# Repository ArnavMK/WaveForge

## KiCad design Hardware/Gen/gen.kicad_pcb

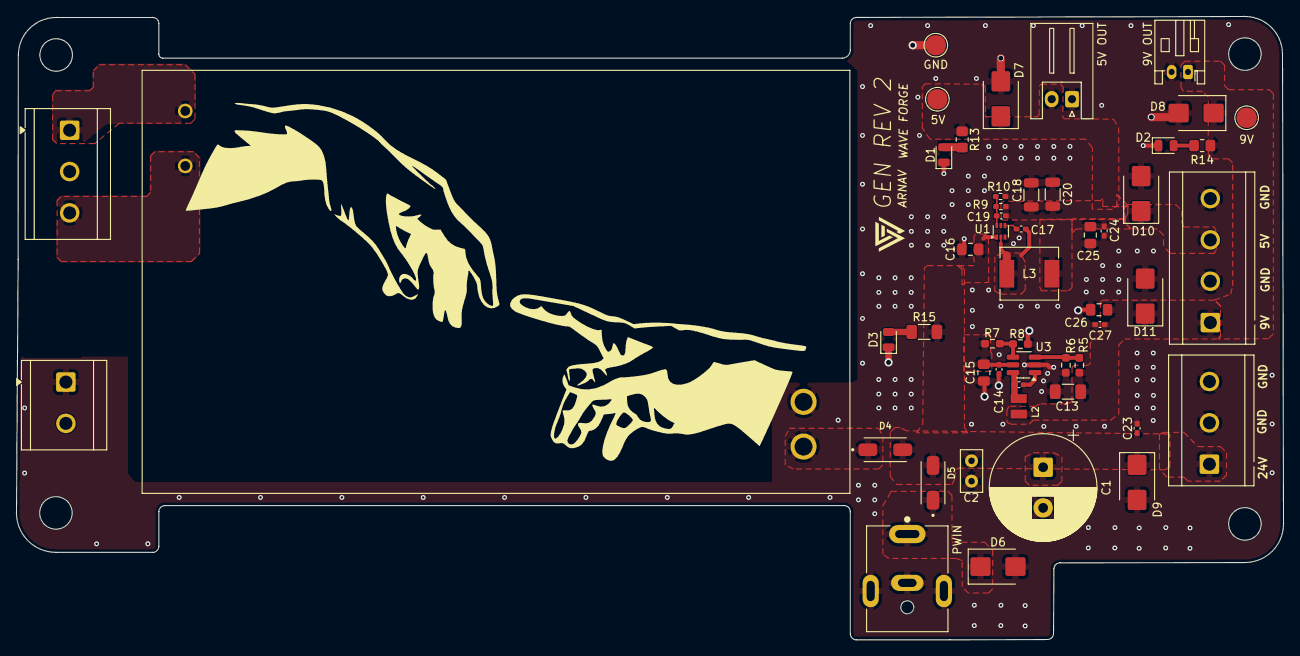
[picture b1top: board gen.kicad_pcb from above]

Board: 2 copper layers, 155.8 x 76.6 mm, 55 parts (0 on the bottom side), 18 nets.

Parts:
5V, 9V: TestPoint; TestPoint_Pad_D2.5mm
5V OUT: SHORI; JST_XH_S2B-XH-A_1x02_P2.50mm_Horizontal
9V OUT: MAE; JST_PH_S2B-PH-K_1x02_P2.00mm_Horizontal
C1: 1000uF; CP_Radial_D13.0mm_P5.00mm
C2: 1uF; C_Disc_D5.0mm_W2.5mm_P2.50mm
C12, C14, C17, C23, C24, C27: 100nF; C_0402_1005Metric_Pad0.74x0.62mm_HandSolder
C13: 15uF; C_1206_3216Metric_Pad1.33x1.80mm_HandSolder
C15: 4.7uF; C_0805_2012Metric_Pad1.18x1.45mm_HandSolder
C16: 3.3uF; C_0805_2012Metric_Pad1.18x1.45mm_HandSolder
C18, C20: 47uF; C_1206_3216Metric
C19: 82pF; C_0402_1005Metric_Pad0.74x0.62mm_HandSolder
C25, C26: 10uF; C_0805_2012Metric_Pad1.18x1.45mm_HandSolder
D1, D2, D3: LED; LED_0805_2012Metric
D4, D5: B340; DIOM5226X240N
D6, D9: SMBJ28A; D_SMB
D7, D8, D10, D11: SMBJ6.0A; D_SMB
GND: TestPoint; TestPoint_Pad_D2.5mm
H1, H2, H3, H3#2: MountingHole; MountingHole_4mm
J1: Screw_Terminal_01x03; TerminalBlock_CUI_TB007-508-03_1x03_P5.08mm_Horizontal
J2: XLR4; TerminalBlock_CUI_TB007-508-04_1x04_P5.08mm_Horizontal
J3: XLR3; TerminalBlock_CUI_TB007-508-03_1x03_P5.08mm_Horizontal
L2: 68uH; WE-LQS_2512
L3: 10uH; IND_SRP6540-100M
MAINS TO GROUND: Screw_Terminal_01x02; TerminalBlock_CUI_TB007-508-02_1x02_P5.08mm_Horizontal
PS1: IRM-90-24; CONV_IRM-90-24
PWIN: PJ-063BH; CUI_PJ-063BH
R5: 178K; R_0603_1608Metric_Pad0.98x0.95mm_HandSolder
R6: 22.1K; R_0603_1608Metric_Pad0.98x0.95mm_HandSolder
R7: 1.37M; R_0603_1608Metric_Pad0.98x0.95mm_HandSolder
R8: 255K; R_0603_1608Metric_Pad0.98x0.95mm_HandSolder
R9: 107K; R_0402_1005Metric_Pad0.72x0.64mm_HandSolder
R10: 13.7K; R_0402_1005Metric_Pad0.72x0.64mm_HandSolder
R13: 300; R_0805_2012Metric_Pad1.20x1.40mm_HandSolder
R14: 680; R_0805_2012Metric_Pad1.20x1.40mm_HandSolder
R15: 2.2K; R_1206_3216Metric_Pad1.30x1.75mm_HandSolder
U1: TPS543021DRLR; SOT-563
U3: TPS560430YDBVR; SOT-23-6_Handsoldering

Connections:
+5V: 5V.1 (1_1), 5V OUT.2, C18.2, C19.1, C20.2, C24.2, C25.2, D7.1 (K), D10.1 (K), J2.3, L3.1, R9.1, R13.2
+9V: 9V.1 (1_1), 9V OUT.1, C13.2, C26.2, C27.2, D8.1 (K), D11.1 (K), J2.1, L2.1, R5.1, R14.2
/ACL: J1.3, PS1.AC_L (AC/L)
/ACN: J1.1, PS1.AC_N (AC/N)
/DC_OUT: C1.1, C2.1, C14.2, C15.2, C16.2, C23.2, D4.1 (K), D5.1 (K), D9.1 (K), J3.1, R7.1, R15.2, U1.1 (VIN), U3.5 (VIN)
GND: 5V OUT.1, 9V OUT.2, C1.2, C2.2, C13.1, C14.1, C15.1, C16.1, C18.1, C20.1, C23.1, C24.1, C25.1, C26.1, C27.1, D1.1 (K), D2.1 (K), D3.1 (K), D6.2 (A), D7.2 (A), D8.2 (A), D9.2 (A), D10.2 (A), D11.2 (A), GND.1 (1_1), J2.2, J2.4, J3.2, J3.3, MAINS TO GROUND.1 (Pin_1_1), PS1.-VO, PWIN.2, PWIN.S1 (SHIELD), PWIN.S2 (SHIELD__1), R6.2, R8.2, R10.2, U1.3 (GND), U3.2 (GND)
unnamed: D1.2 (A), R13.1
unnamed: D2.2 (A), R14.1
unnamed: D3.2 (A), R15.1
unnamed: D4.2 (A), PS1.+VO
unnamed: D5.2 (A), D6.1 (K), PWIN.1
unnamed: C17.2, U1.4 (BOOT)
unnamed: C19.2, R9.2, R10.1, U1.6 (FB)
unnamed: C17.1, L3.2, U1.2 (SW)
unnamed: C12.2, U3.1 (CB)
unnamed: R7.2, R8.1, U3.4 (EN)
unnamed: R5.2, R6.1, U3.3 (FB)
unnamed: C12.1, L2.2, U3.6 (SW)

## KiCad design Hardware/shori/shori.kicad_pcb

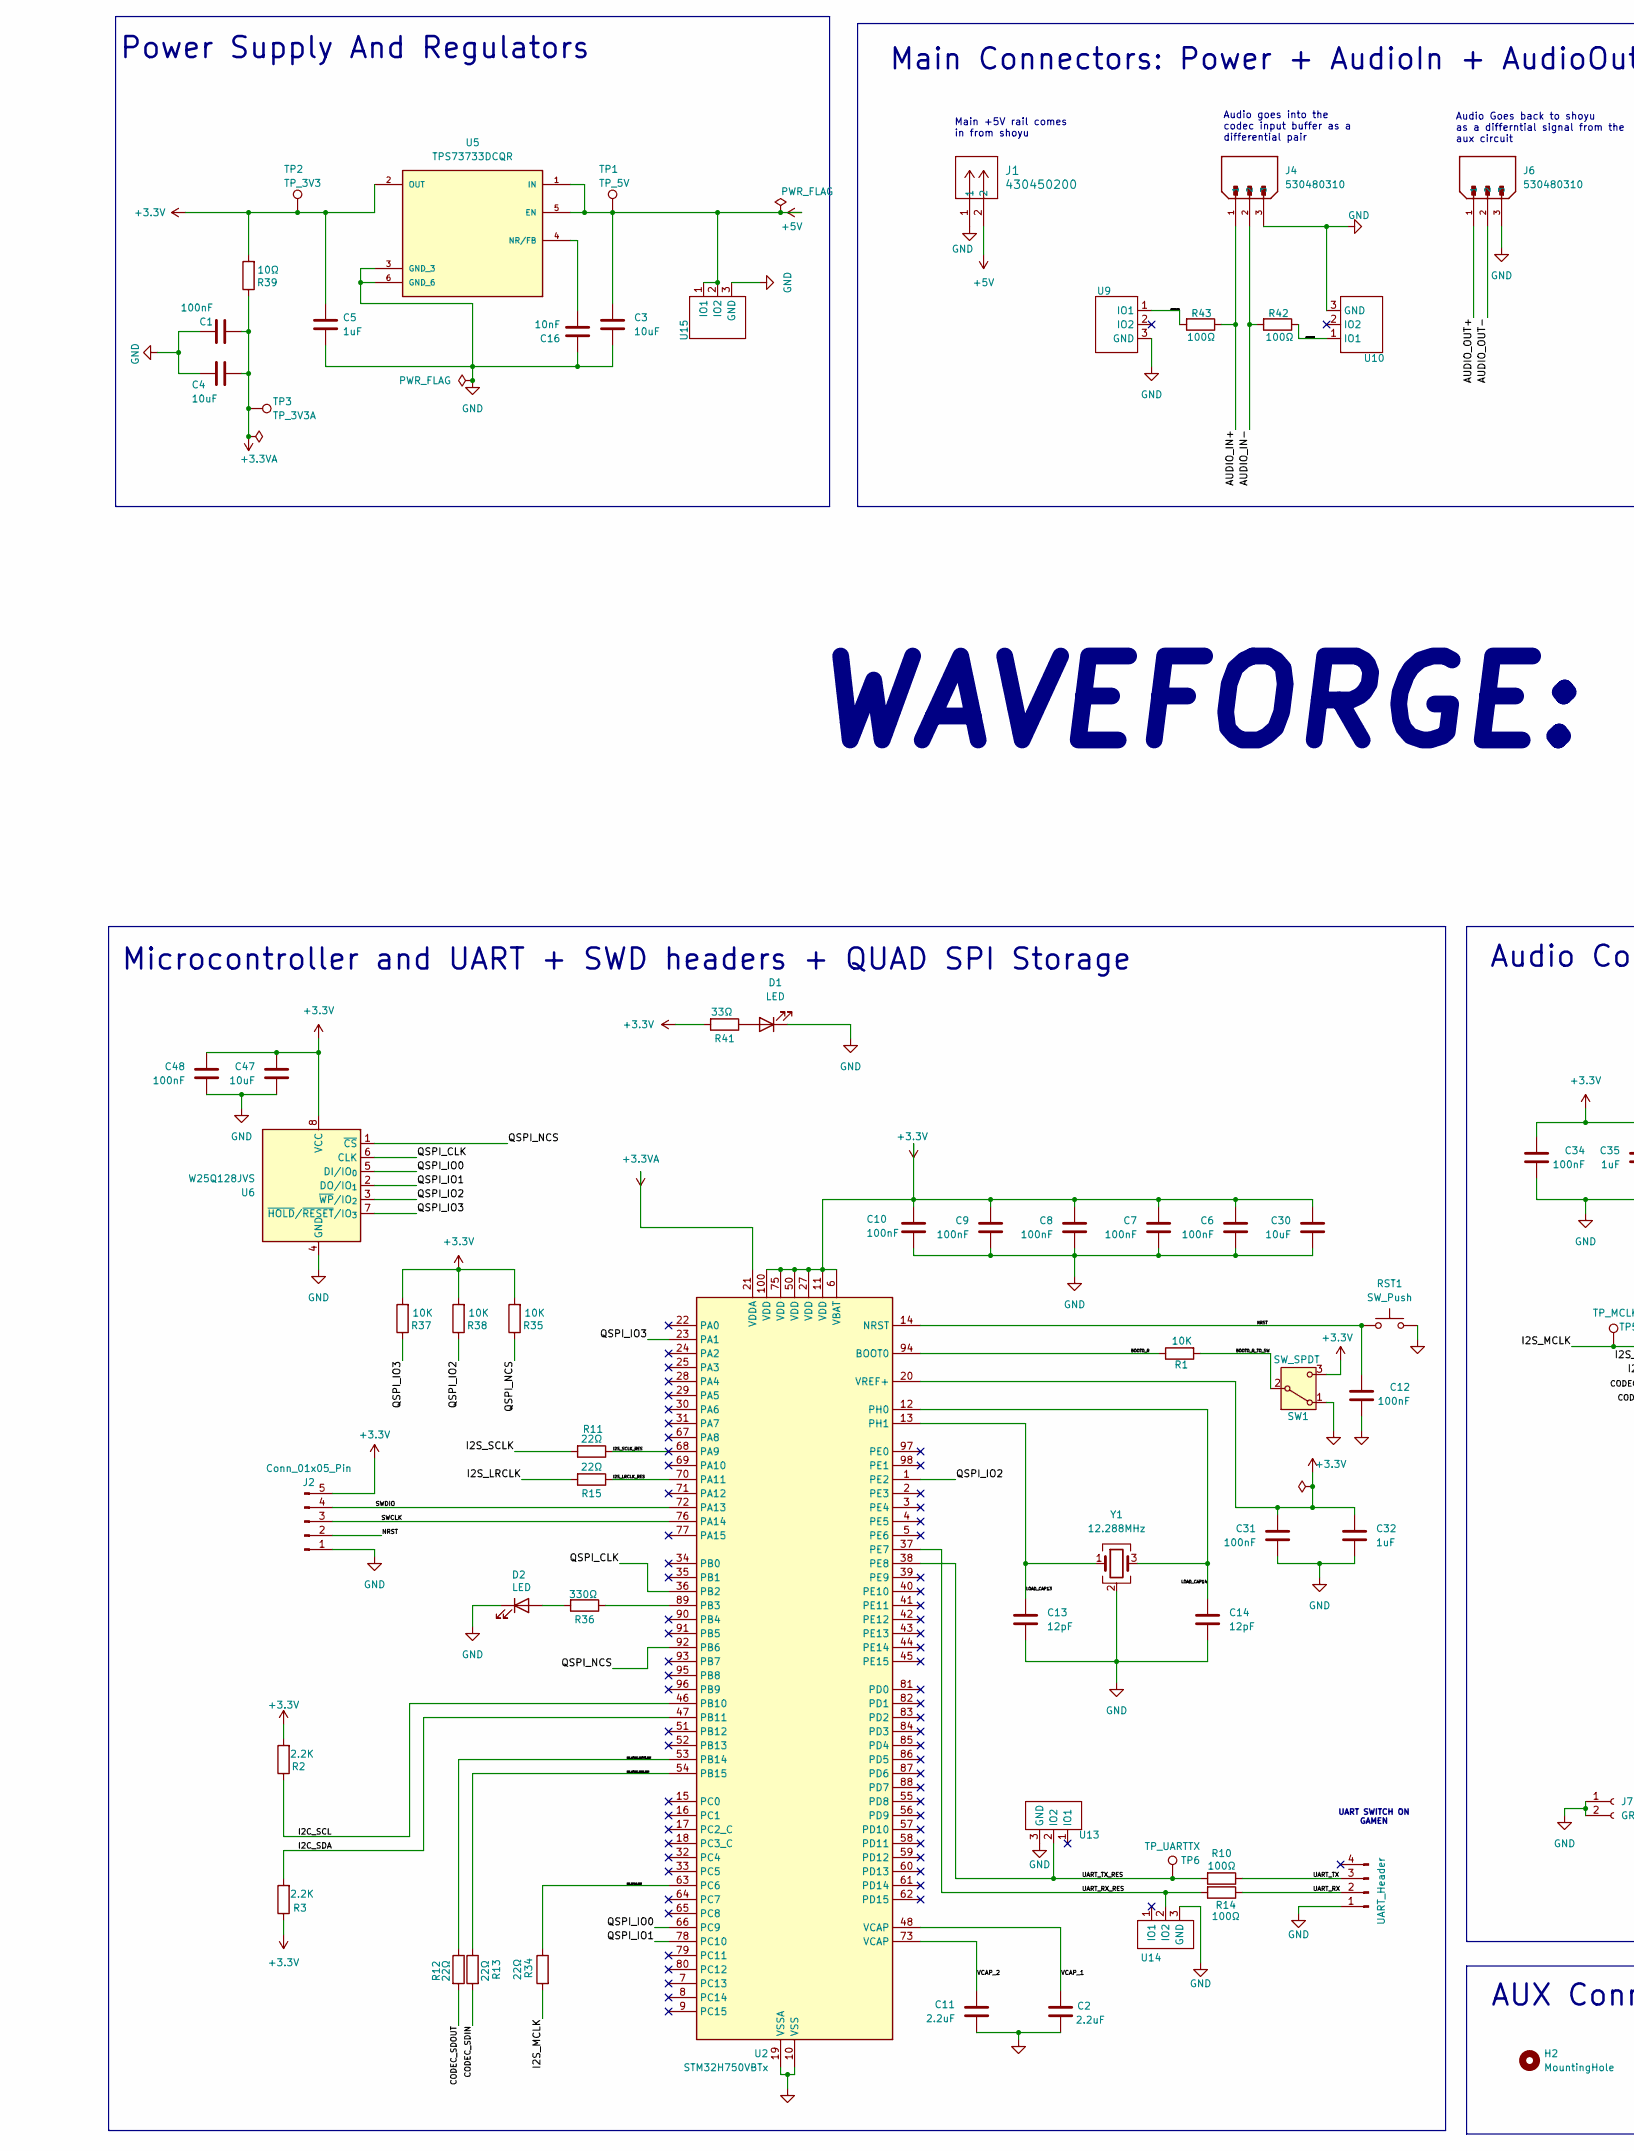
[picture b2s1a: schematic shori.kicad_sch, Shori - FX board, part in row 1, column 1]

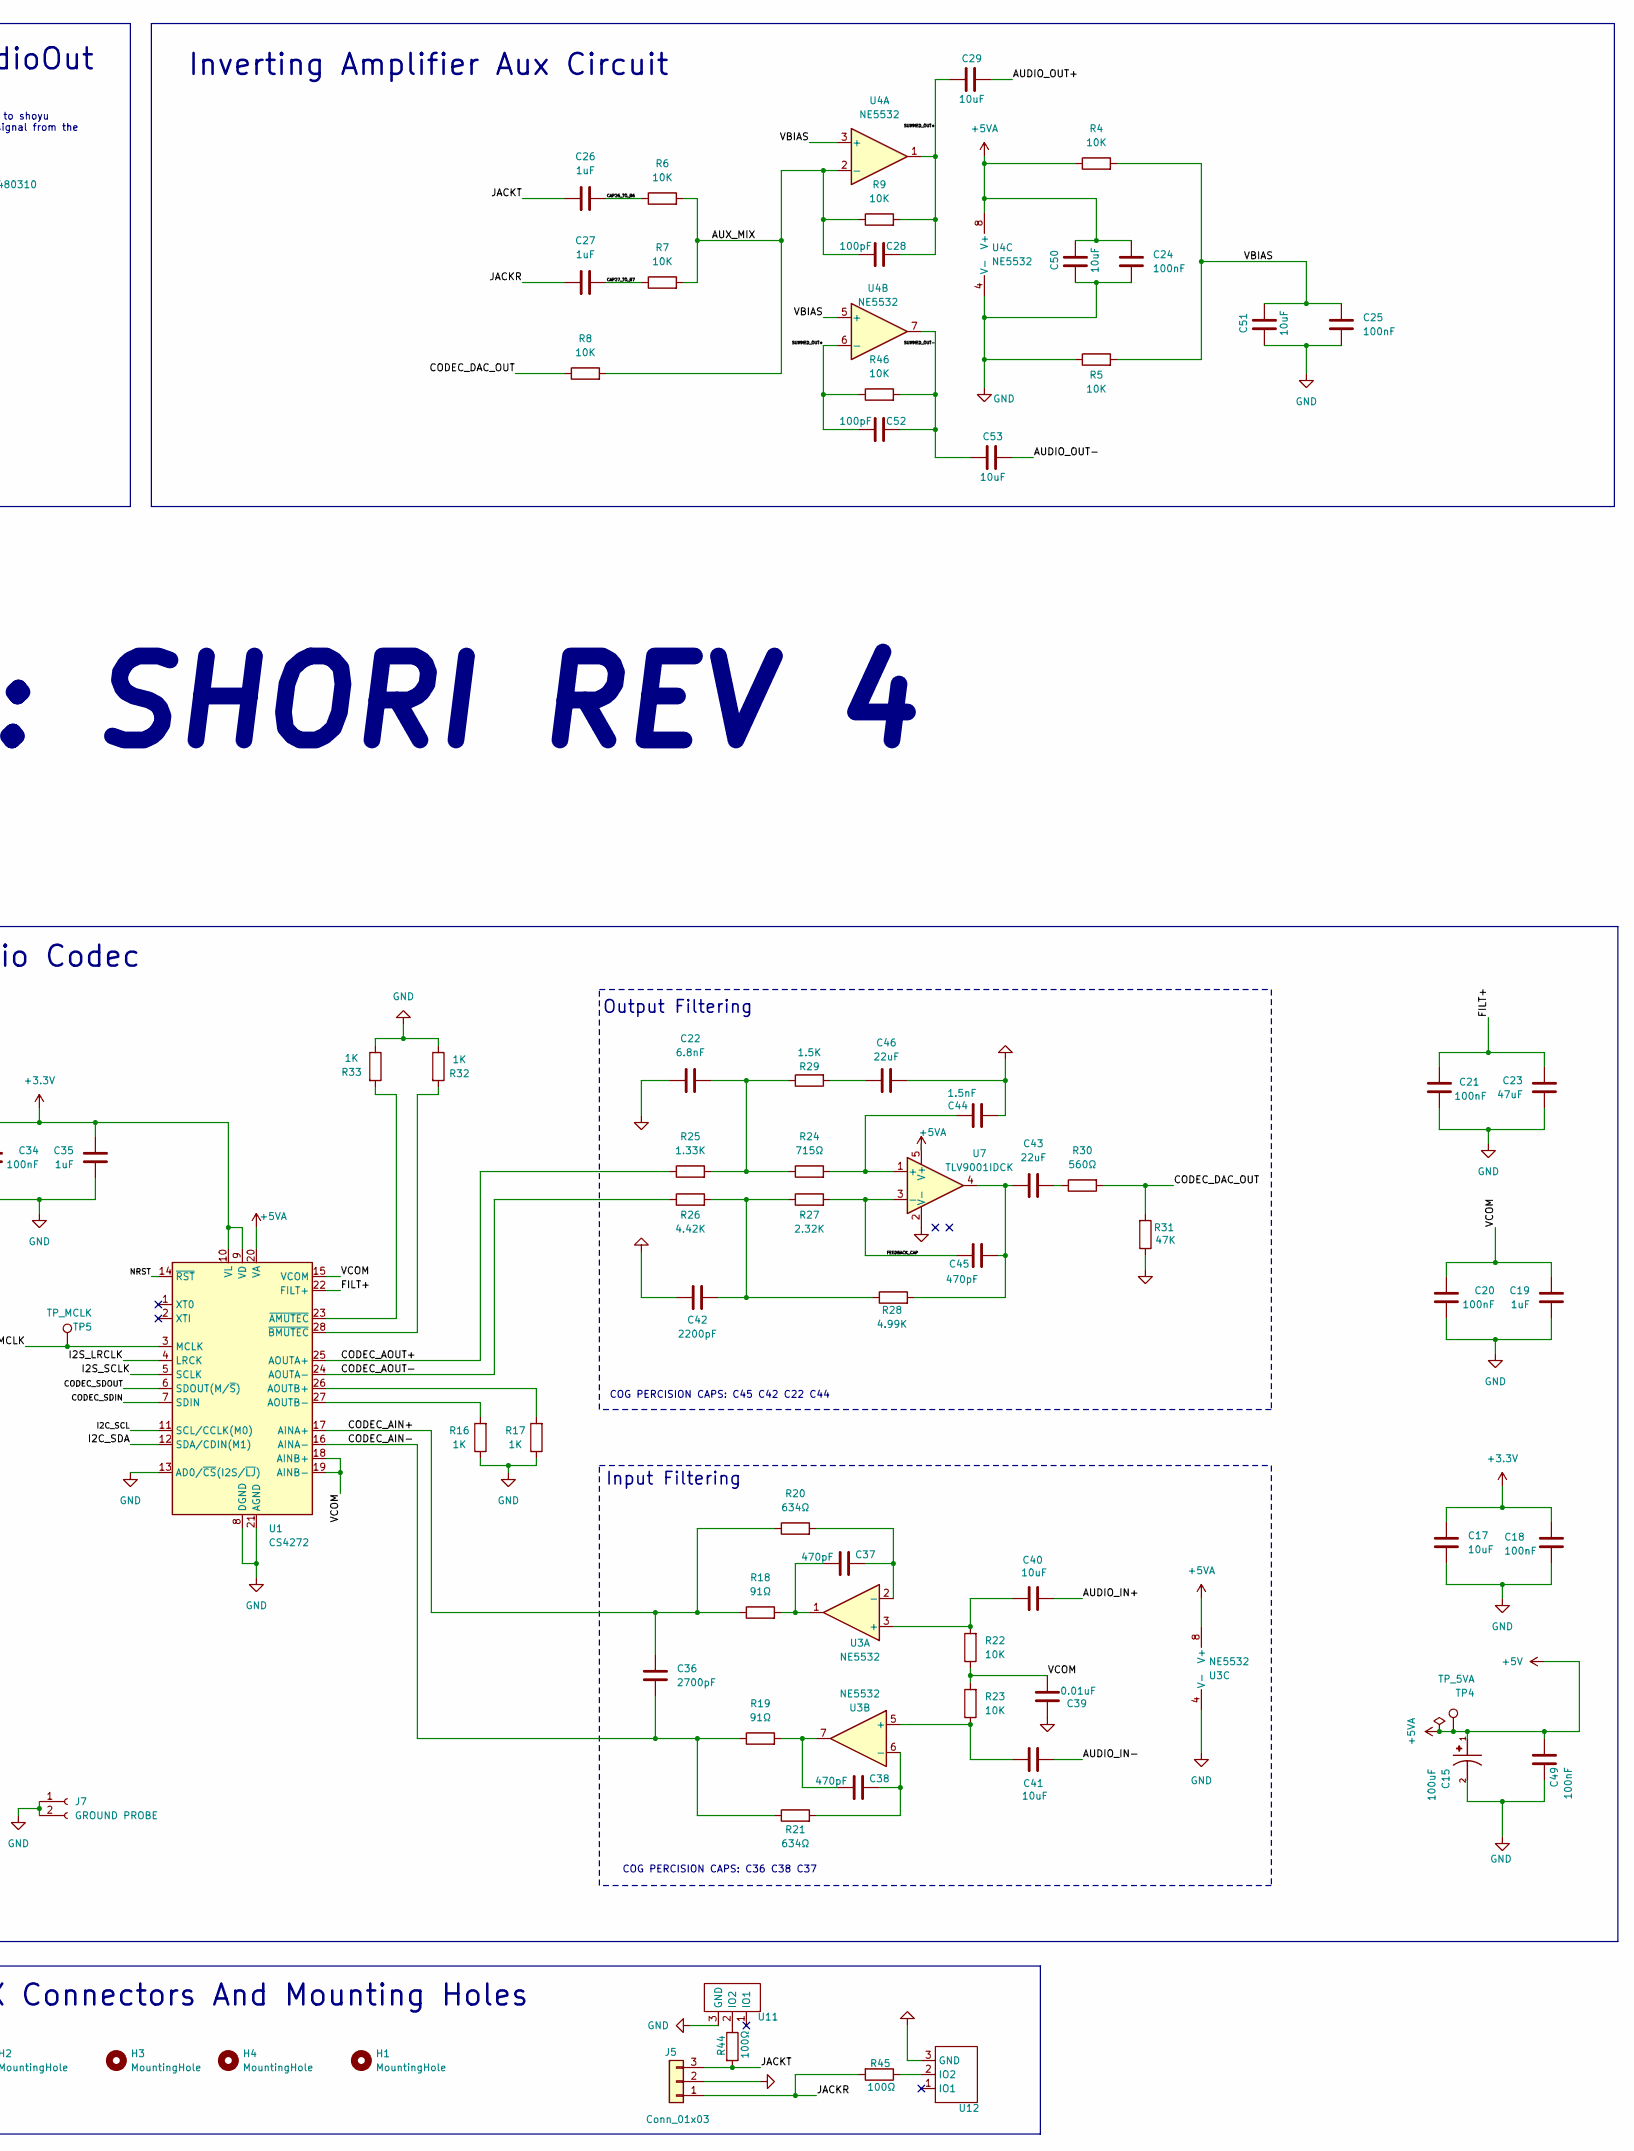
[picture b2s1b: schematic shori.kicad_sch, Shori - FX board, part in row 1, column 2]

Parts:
C1, C6, C7, C8, C9, C10, C12, C18, C20, C21, C24, C25, C31, C34, C48, C49: 100nF; C_0402_1005Metric_Pad0.74x0.62mm_HandSolder
C2, C11: 2.2uF; C_0402_1005Metric_Pad0.74x0.62mm_HandSolder
C3, C4, C17, C29, C30, C40, C41, C47, C50, C51, C53: 10uF; C_0805_2012Metric
C5, C19, C26, C27, C32, C35: 1uF; C_0402_1005Metric_Pad0.74x0.62mm_HandSolder
C13, C14: 12pF; C_0402_1005Metric_Pad0.74x0.62mm_HandSolder
C15: 100uF; CAPMP6.3X3.2_2.8N_KEM; PARTREV 3
C16: 10nF; C_0402_1005Metric_Pad0.74x0.62mm_HandSolder
C22: 6.8nF; C_0402_1005Metric_Pad0.74x0.62mm_HandSolder
C23: 47uF; C_1206_3216Metric
C28, C52: 100pF; C_0402_1005Metric_Pad0.74x0.62mm_HandSolder
C36: 2700pF; C_0402_1005Metric_Pad0.74x0.62mm_HandSolder
C37, C38, C45: 470pF; C_0402_1005Metric_Pad0.74x0.62mm_HandSolder
C39: 0.01uF; C_0402_1005Metric_Pad0.74x0.62mm_HandSolder
C42: 2200pF; C_0402_1005Metric_Pad0.74x0.62mm_HandSolder
C43, C46: 22uF; C_1206_3216Metric
C44: 1.5nF; C_0402_1005Metric_Pad0.74x0.62mm_HandSolder
D1: LED; LED_0805_2012Metric_Pad1.15x1.40mm_HandSolder
D2: LED; LED_0402_1005Metric_Pad0.77x0.64mm_HandSolder
H1, H2, H3, H4: MountingHole; MountingHole_3.5mm
J1: 430450200; JST_XH_S2B-XH-A_1x02_P2.50mm_Horizontal
J2: Conn_01x05_Pin; PinHeader_1x05_P2.54mm_Vertical
J3: UART_Header; MOLEX_530480310
J4, J6: 530480310; MOLEX_530480310; PARTREV A
J5: Conn_01x03; JST_PH_S3B-PH-K_1x03_P2.00mm_Horizontal
J7: GROUND PROBE; PinSocket_1x02_P2.00mm_Vertical
R1, R4, R5, R6, R7, R8, R9, R22, R23, R35, R37, R38, R46: 10K; R_0402_1005Metric_Pad0.72x0.64mm_HandSolder
R2, R3: 2.2K; R_0402_1005Metric_Pad0.72x0.64mm_HandSolder
R10, R14, R42, R43, R44, R45: 100Ω; R_0402_1005Metric_Pad0.72x0.64mm_HandSolder
R11, R12, R13, R15, R34: 22Ω; R_0402_1005Metric_Pad0.72x0.64mm_HandSolder
R16, R17, R32, R33: 1K; R_0402_1005Metric_Pad0.72x0.64mm_HandSolder
R18, R19: 91Ω; R_0402_1005Metric_Pad0.72x0.64mm_HandSolder
R20, R21: 634Ω; R_0402_1005Metric_Pad0.72x0.64mm_HandSolder
R24: 715Ω; R_0402_1005Metric_Pad0.72x0.64mm_HandSolder
R25: 1.33K; R_0402_1005Metric_Pad0.72x0.64mm_HandSolder
R26: 4.42K; R_0402_1005Metric_Pad0.72x0.64mm_HandSolder
R27: 2.32K; R_0402_1005Metric_Pad0.72x0.64mm_HandSolder
R28: 4.99K; R_0402_1005Metric_Pad0.72x0.64mm_HandSolder
R29: 1.5K; R_0402_1005Metric_Pad0.72x0.64mm_HandSolder
R30: 560Ω; R_0402_1005Metric_Pad0.72x0.64mm_HandSolder
R31: 47K; R_0402_1005Metric_Pad0.72x0.64mm_HandSolder
R36: 330Ω; R_0402_1005Metric_Pad0.72x0.64mm_HandSolder
R39: 10Ω; R_0402_1005Metric_Pad0.72x0.64mm_HandSolder
R41: 33Ω; R_0402_1005Metric_Pad0.72x0.64mm_HandSolder
RST1: SW_Push; SW_SPST_B3U-1000P
SW1: SW_SPDT; PinHeader_1x03_P2.54mm_Vertical
TP1: TP_5V; TestPoint_Pad_D1.0mm
TP2: TP_3V3; TestPoint_Pad_D1.0mm
TP3: TP_3V3A; TestPoint_Pad_D1.0mm
TP4: TP_5VA; TestPoint_Pad_D1.0mm
TP5: TP_MCLK; TestPoint_Pad_D1.0mm
TP6: TP_UARTTX; TestPoint_Pad_D1.0mm
U1: CS4272; TSSOP-28_4.4x9.7mm_P0.65mm
U2: STM32H750VBTx; LQFP-100_14x14mm_P0.5mm
U3, U4: NE5532; SOIC-8_3.9x4.9mm_P1.27mm
U5: TPS73733DCQR; IC_TPS73733DCQR; PARTREV R
U6: W25Q128JVS; SOIC-8_5.3x5.3mm_P1.27mm
U7: TLV9001IDCK; SOT-353_SC-70-5
U9, U10, U11, U12, U13, U14, U15: SOT-23-3
Y1: 12.288MHz; Crystal_SMD_3225-4Pin_3.2x2.5mm

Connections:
+3.3V: C5.1, C6.1, C7.1, C8.1, C9.1, C10.1, C17.1, C18.1, C30.1, C31.1, C32.1, C34.1, C35.1, C47.1, C48.1, J2.5, R2.2, R3.1, R35.2, R37.2, R38.2, R39.2, R41.2, SW1.3 (C), TP2.1 (1_1), U1.9 (VD), U1.10 (VL), U2.6 (VBAT), U2.11 (VDD), U2.20 (VREF+), U2.27 (VDD), U2.50 (VDD), U2.75 (VDD), U2.100 (VDD), U5.2 (OUT), U6.8 (VCC); also elsewhere on the board
+3.3VA: C1.1, C4.1, R39.1, TP3.1 (1_1), U2.21 (VDDA)
+5V: C3.1, C15.1, C24.1, C49.1, C50.2, J1.2, R4.1, TP1.1 (1_1), TP4.1 (1_1), U1.20 (VA), U3.8 (V+), U4.8 (V+), U5.1 (IN), U5.5 (EN), U7.5 (V+), U15.1 (IO1), U15.2 (IO2)
/AUDIO_IN+: C40.2, J4.1, R43.1
/AUDIO_IN-: C41.2, J4.2, R42.2
/AUDIO_OUT+: C29.2, J6.1
/AUDIO_OUT-: C53.2, J6.2
/AUX_MIX: C28.1, R6.2, R7.2, R8.2, R9.1, U4.2 (-)
/BOOT0_R: R1.1, U2.94 (BOOT0)
/BOOT0_R_TO_SW: R1.2, SW1.2 (B); also elsewhere on the board
/CAP26_TO_R6: C26.2, R6.1
/CAP27_TO_R7: C27.2, R7.1
/CODEC_AIN+: C36.1, R18.1, R20.1, U1.17 (AINA+)
/CODEC_AIN-: C36.2, R19.1, R21.1, U1.16 (AINA-)
/CODEC_AOUT+: R25.1, U1.25 (AOUTA+)
/CODEC_AOUT-: R26.1, U1.24 (AOUTA-)
/CODEC_DAC_OUT: R8.1, R30.2, R31.2
/CODEC_SDIN: R13.2, U1.7 (SDIN)
/CODEC_SDOUT: R12.2, U1.6 (SDOUT(M/~S))
/FEEDBACK_CAP: C45.1, R27.2, U7.3 (-)
/FILT+: C21.1, C23.1, U1.22 (FILT+)
/I2C_SCL: R2.1, U1.11 (SCL/CCLK(M0)), U2.46 (PB10)
/I2C_SDA: R3.2, U1.12 (SDA/CDIN(M1)), U2.47 (PB11)
/I2S_CODEC_SDIN_RES: R13.1, U2.54 (PB15)
/I2S_CODEC_SDOUT_RES: R12.1, U2.53 (PB14)
/I2S_LRCLK: R15.2, U1.4 (LRCK)
/I2S_LRCLK_RES: R15.1, U2.70 (PA11)
/I2S_MCLK: R34.2, TP5.1 (1_1), U1.3 (MCLK)
/I2S_MCLK_RES: R34.1, U2.63 (PC6)
/I2S_SCLK: R11.2, U1.5 (SCLK)
/I2S_SCLK_RES: R11.1, U2.68 (PA9)
/JACKR: C27.1, J5.1, R45.2
/JACKT: C26.1, J5.3, R44.2
/LOAD_CAP13: C13.1, U2.13 (PH1), Y1.1
/LOAD_CAP14: C14.1, U2.12 (PH0), Y1.3
/NRST: C12.1, J2.2, RST1.1, U1.14 (~RST), U2.14 (NRST)
/QSPI_CLK: U2.36 (PB2), U6.6 (CLK)
/QSPI_IO0: U2.66 (PC9), U6.5 (DI/IO_{0})
/QSPI_IO1: U2.78 (PC10), U6.2 (DO/IO_{1})
/QSPI_IO2: R38.1, U2.1 (PE2), U6.3 (~WP/IO_{2})
/QSPI_IO3: R37.1, U2.23 (PA1), U6.7 (~HOLD/~RESET/IO_{3})
/QSPI_NCS: R35.1, U2.92 (PB6), U6.1 (~CS)
/SHUNT_RES_AINM: R42.1, U10.1 (IO1)
/SHUNT_RES_AINP: R43.2, U9.1 (IO1)
/SUMMED_OUT+: C28.2, C29.1, C52.1, R9.2, R46.1, U4.1, U4.6 (-)
/SUMMED_OUT-: C52.2, C53.1, R46.2, U4.7
/SWCLK: J2.3, U2.76 (PA14)
/SWDIO: J2.4, U2.72 (PA13)
/UART_RX: J3.2, R14.1
/UART_RX_RES: R14.2, U2.37 (PE7), U14.2 (IO2)
/UART_TX: J3.3, R10.1
/UART_TX_RES: R10.2, TP6.1 (1_1), U2.38 (PE8), U13.2 (IO2)
/VBIAS: C25.1, C51.2, R4.2, R5.2, U4.3 (+), U4.5 (+)
/VCAP_1: C2.2, U2.48 (VCAP)
/VCAP_2: C11.2, U2.73 (VCAP)
/VCOM: C19.1, C20.1, C39.1, R22.1, R23.2, U1.15 (VCOM), U1.18 (AINB+), U1.19 (AINB-)
GND: C1.2, C2.1, C3.2, C4.2, C5.2, C6.2, C7.2, C8.2, C9.2, C10.2, C11.1, C12.2, C13.2, C14.2, C15.2, C16.1, C17.2, C18.2, C19.2, C20.2, C21.2, C22.1, C23.2, C24.2, C25.2, C30.2, C31.2, C32.2, C34.2, C35.2, C39.2, C42.1, C44.2, C46.2, C47.2, C48.2, C49.2, C50.1, C51.1, D1.1 (K), D2.1 (K), J1.1, J2.1, J3.1, J4.3, J5.2, J6.3, J7.1, J7.2, R5.1, R16.1, R17.1, R31.1, R32.1, R33.1, RST1.2, SW1.1 (A), U1.8 (DGND), U1.13 (AD0/~CS(I2S/~LJ)), U1.21 (AGND), U2.10 (VSS), U2.19 (VSSA), U2.26 (VSS), U2.49 (VSS), U2.74 (VSS), U2.99 (VSS), U3.4 (V-), U4.4 (V-), U5.3 (GND_3), U5.6 (GND_6), U6.4 (GND), U7.2 (V-), U9.3 (GND), U10.3 (GND), U11.3 (GND), U12.3 (GND), U13.3 (GND), U14.3 (GND), U15.3 (GND), Y1.2 (G), Y1.4 (G); also elsewhere on the board
unnamed: C22.2, R24.1, R25.2, R29.1
unnamed: C37.1, R18.2, U3.1
unnamed: C38.1, R19.2, U3.7
unnamed: C42.2, R26.2, R27.1, R28.1
unnamed: C43.1, C45.2, R28.2, U7.4
unnamed: C43.2, R30.1
unnamed: C46.1, R29.2
unnamed: D1.2 (A), R41.1
unnamed: D2.2 (A), R36.2
unnamed: R17.2, U1.26 (AOUTB+)
unnamed: R16.2, U1.27 (AOUTB-)
unnamed: R33.2, U1.23 (~AMUTEC)
unnamed: R32.2, U1.28 (~BMUTEC)
unnamed: R36.1, U2.89 (PB3)
unnamed: C40.1, R22.2, U3.3 (+)
unnamed: C37.2, R20.2, U3.2 (-)
unnamed: C41.1, R23.1, U3.5 (+)
unnamed: C38.2, R21.2, U3.6 (-)
unnamed: C16.2, U5.4 (NR/FB)
unnamed: C44.1, R24.2, U7.1 (+)
unnamed: R44.1, U11.2 (IO2)
unnamed: R45.1, U12.2 (IO2)

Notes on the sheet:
Audio Goes back to shoyu as a differntial signal from the aux circuit
Audio Codec
Inverting Amplifier Aux Circuit
Audio goes into the codec input buffer as a differential pair
WAVEFORGE: SHORI REV 4
Microcontroller and UART + SWD headers + QUAD SPI Storage
Power Supply And Regulators
Output Filtering
Main Connectors: Power + AudioIn + AudioOut
UART SWITCH ON GAMEN
COG PERCISION CAPS: C36 C38 C37
AUX Connectors And Mounting Holes
Main +5V rail comes in from shoyu
Input Filtering
COG PERCISION CAPS: C45 C42 C22 C44

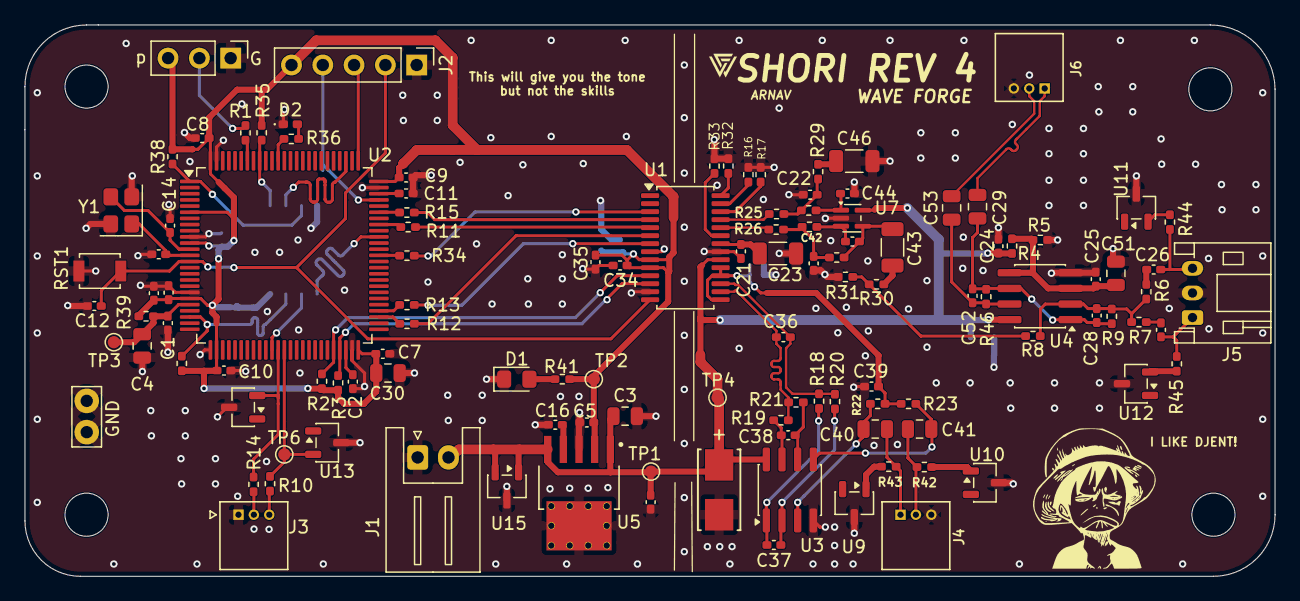
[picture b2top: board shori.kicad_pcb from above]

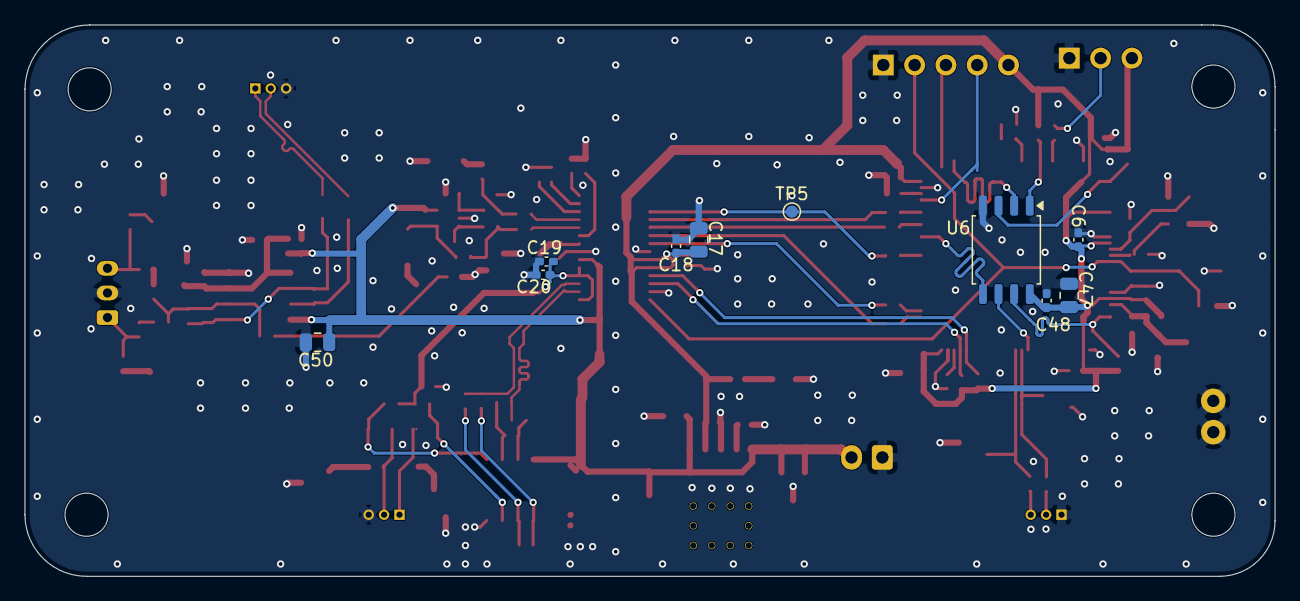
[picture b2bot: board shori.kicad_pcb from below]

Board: 4 copper layers, 101.5 x 44.8 mm, 133 parts (10 on the bottom side), 79 nets.

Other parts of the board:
GND: TestPoint_Bridge_Pitch2.54mm_Drill1.0mm
p: SW_SPDT; PinHeader_1x03_P2.54mm_Vertical

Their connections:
+3.3V: p.3 (C); also elsewhere on the board
/BOOT0_R_TO_SW: p.2 (B); also elsewhere on the board
GND: GND.1, p.1 (A); also elsewhere on the board

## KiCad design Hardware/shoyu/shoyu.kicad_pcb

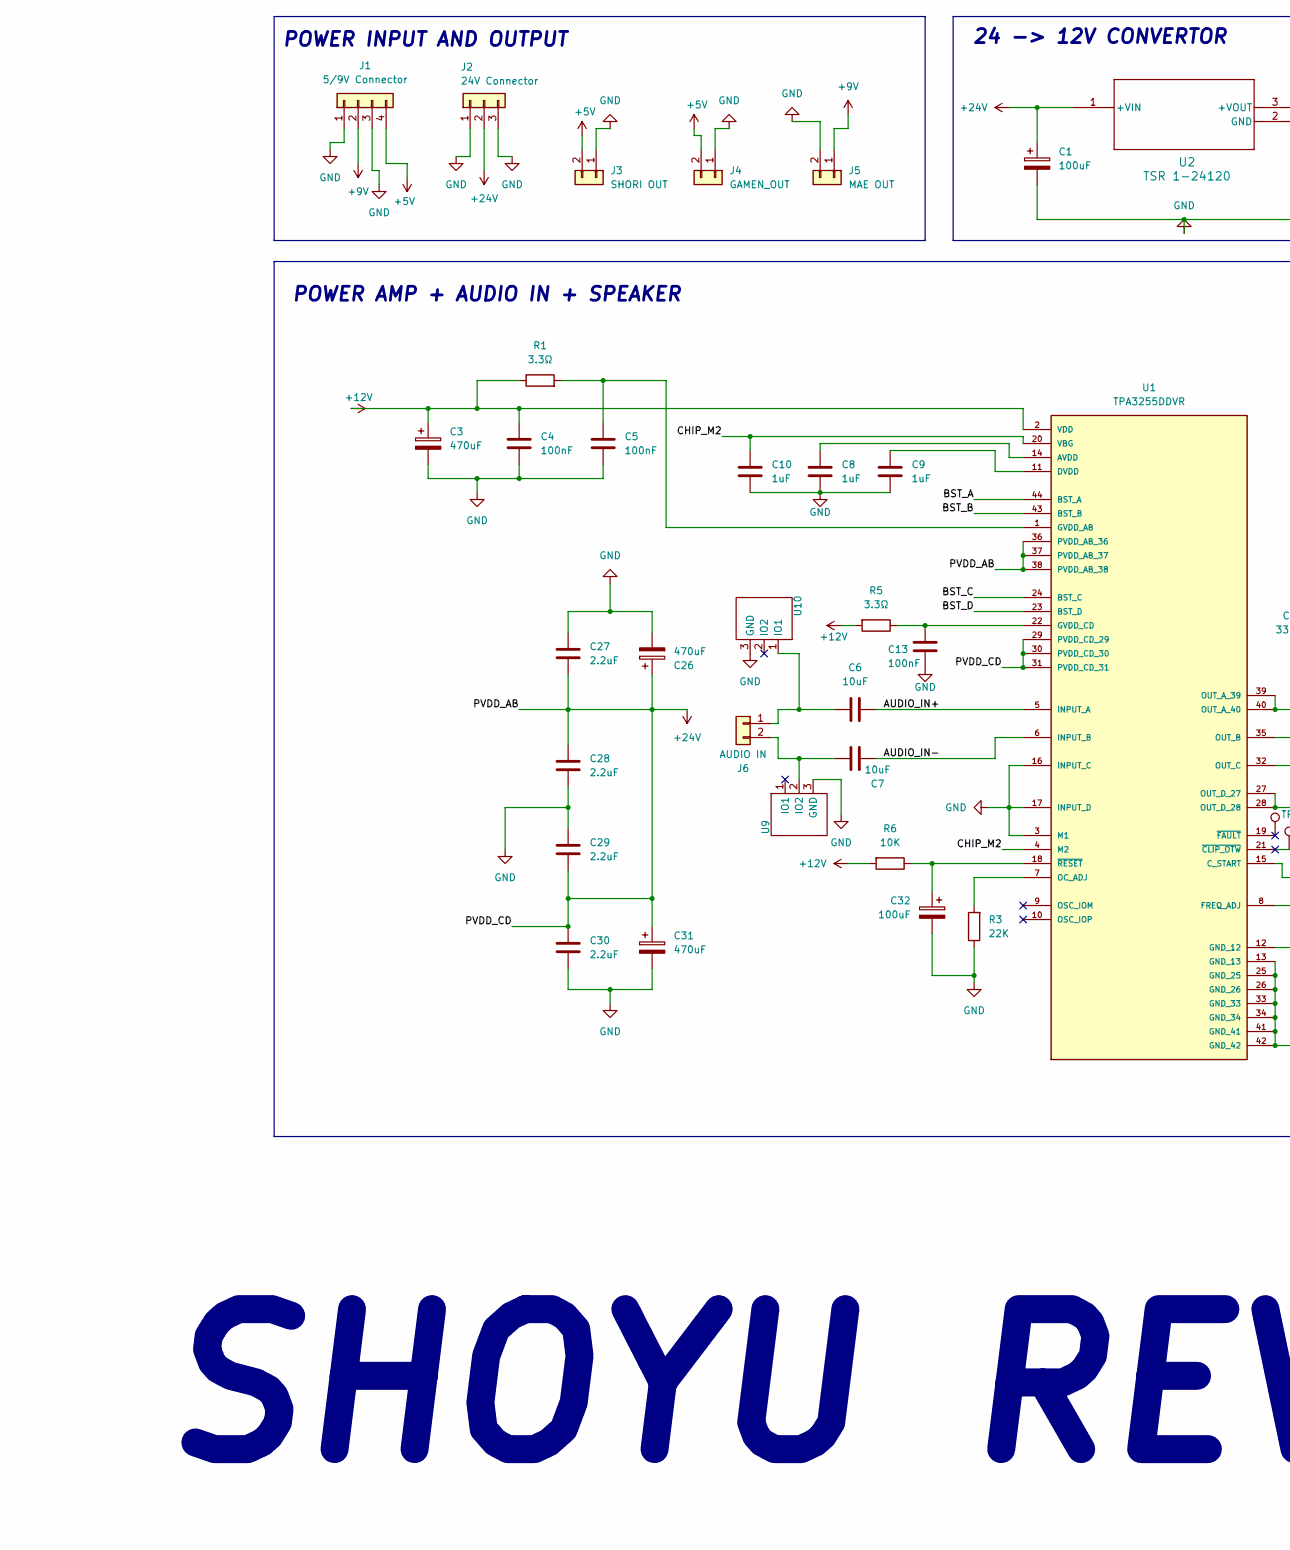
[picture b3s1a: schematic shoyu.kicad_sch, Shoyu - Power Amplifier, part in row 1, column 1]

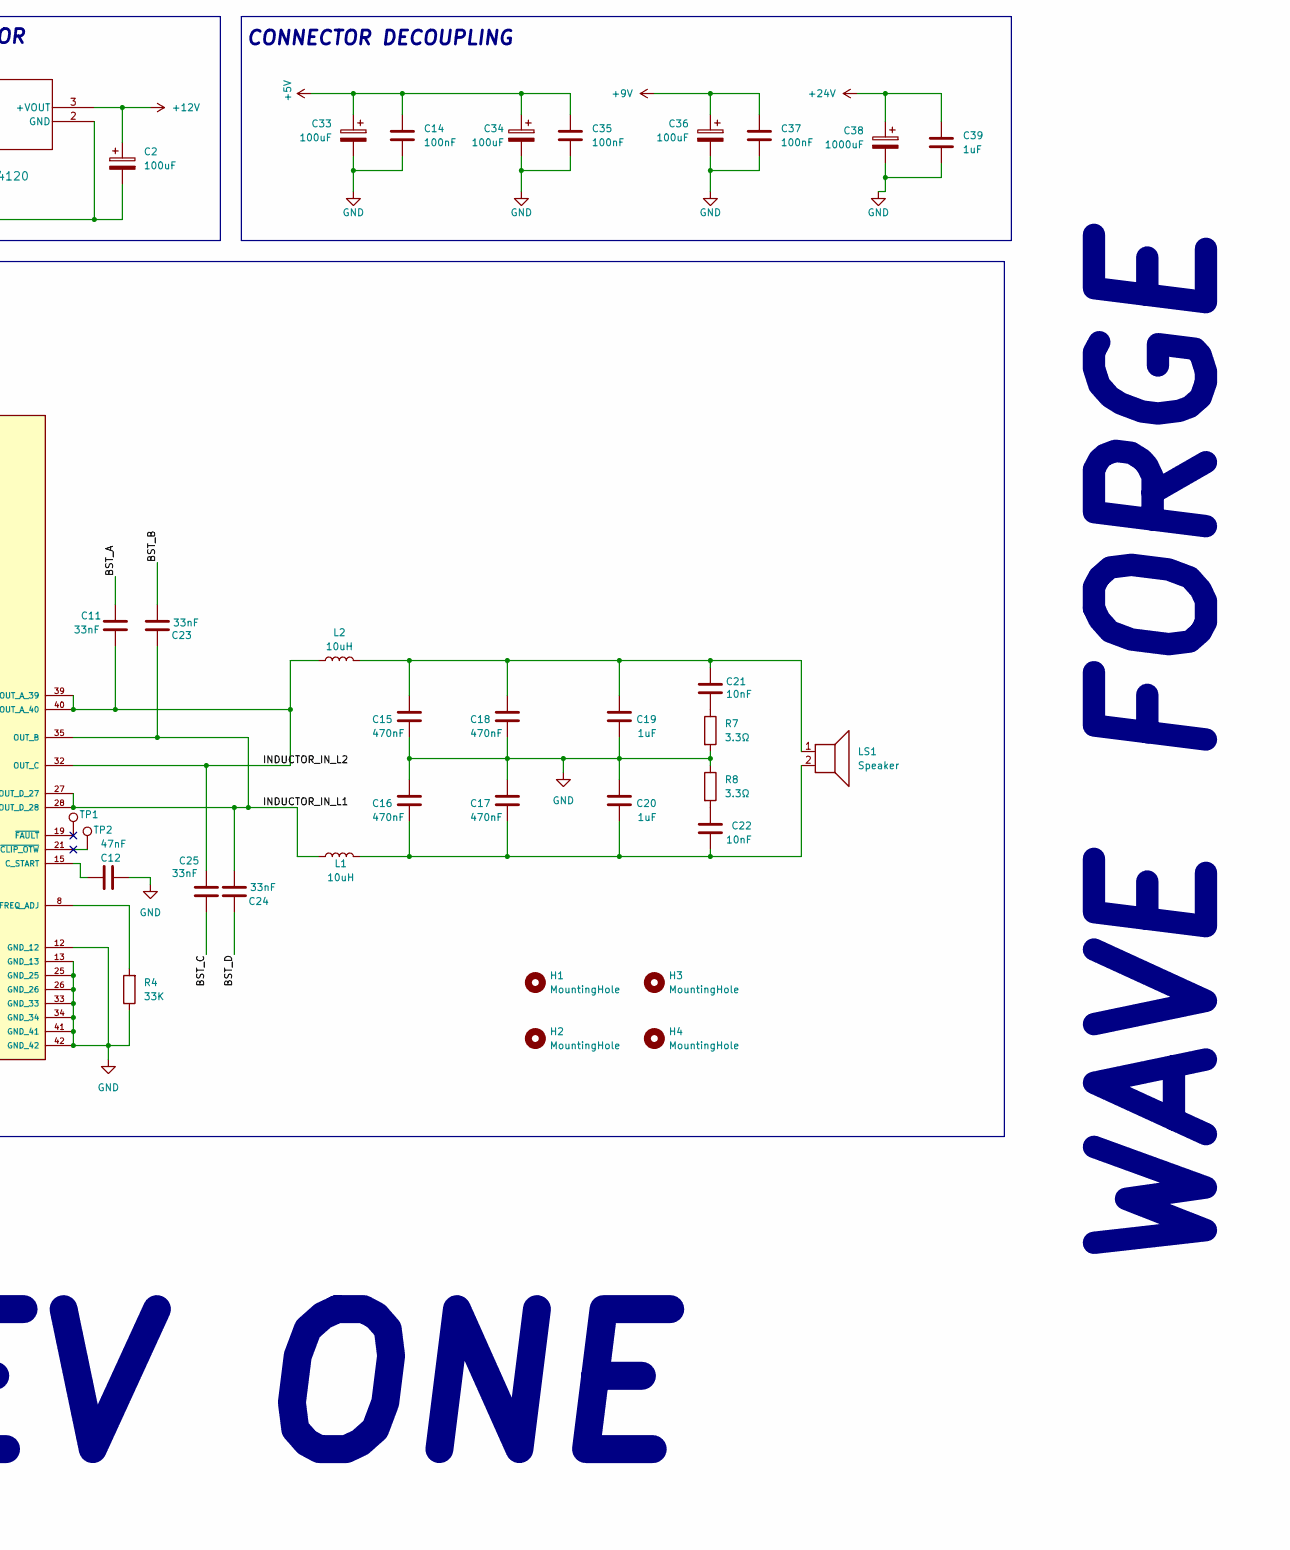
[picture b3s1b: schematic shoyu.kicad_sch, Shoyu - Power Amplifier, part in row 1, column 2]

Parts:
C1, C2, C32, C33, C34, C36: 100uF; CP_Radial_D8.0mm_P3.50mm
C3, C26, C31: 470uF; CP_Radial_D10.0mm_P5.00mm
C4, C5, C13, C14, C35, C37: 100nF; C_0402_1005Metric_Pad0.74x0.62mm_HandSolder
C6, C7: 10uF; C_0805_2012Metric_Pad1.18x1.45mm_HandSolder
C8, C9, C10: 1uF; C_0603_1608Metric
C11, C23, C24, C25: 33nF; C_0402_1005Metric_Pad0.74x0.62mm_HandSolder
C12: 47nF; C_0402_1005Metric_Pad0.74x0.62mm_HandSolder
C15, C16, C17, C18: 470nF; C_Rect_L7.2mm_W3.5mm_P5.00mm
C19, C20, C39: 1uF; C_0603_1608Metric_Pad1.08x0.95mm_HandSolder
C21, C22: 10nF; C_0402_1005Metric_Pad0.74x0.62mm_HandSolder
C27, C28, C29, C30: 2.2uF; C_0603_1608Metric
C38: 1000uF; CP_Radial_D12.5mm_P5.00mm
H1, H2, H3, H4: MountingHole; MountingHole_2mm
J1: 5/9V Connector; JST_XH_S4B-XH-A_1x04_P2.50mm_Horizontal
J2: 24V Connector; JST_XH_S3B-XH-A_1x03_P2.50mm_Horizontal
J3: SHORI OUT; JST_XH_S2B-XH-A_1x02_P2.50mm_Horizontal
J4: GAMEN_OUT; JST_XH_S2B-XH-A_1x02_P2.50mm_Horizontal
J5: MAE OUT; JST_XH_S2B-XH-A_1x02_P2.50mm_Horizontal
J6: AUDIO IN; JST_PH_S2B-PH-K_1x02_P2.00mm_Horizontal
L1, L2: 10uH; IND_SRP1038A_BRN-M
LS1: Speaker; TerminalBlock_CUI_TB007-508-02_1x02_P5.08mm_Horizontal
R1, R5, R7, R8: 3.3Ω; R_0402_1005Metric_Pad0.72x0.64mm_HandSolder
R3: 22K; R_0402_1005Metric_Pad0.72x0.64mm_HandSolder
R4: 33K; R_0402_1005Metric_Pad0.72x0.64mm_HandSolder
R6: 10K; R_0402_1005Metric_Pad0.72x0.64mm_HandSolder
TP1, TP2: TestPoint
U1: TPA3255DDVR; HTSSOP-44_6.1x14mm_P0.635mm_TopEP4.14x7.01mm; PARTREV A
U2: TSR 1-24120; TSR1-SINGLE_TRP
U9, U10: SOT-23-3

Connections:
+5V: C14.1, C33.1, C34.1, C35.1, J1.4, J3.2, J4.2
+9V: C36.1, C37.1, J1.2, J5.1
+12V: C2.1, C3.1, C4.1, R1.1, R5.2, R6.2, U1.2 (VDD), U2.3 (+VOUT)
+24V: C1.1, C26.1, C27.2, C28.1, C29.2, C30.1, C31.1, C38.1, C39.1, J2.2, U1.29 (PVDD_CD_29), U1.30 (PVDD_CD_30), U1.31 (PVDD_CD_31), U1.36 (PVDD_AB_36), U1.37 (PVDD_AB_37), U1.38 (PVDD_AB_38), U2.1 (+VIN)
/AUDIO_IN+: C6.2, U1.5 (INPUT_A)
/AUDIO_IN-: C7.2, U1.6 (INPUT_B)
/BST_A: C11.1, U1.44 (BST_A)
/BST_B: C23.2, U1.43 (BST_B)
/BST_C: C25.2, U1.24 (BST_C)
/BST_D: C24.1, U1.23 (BST_D)
/CHIP_M2: C10.1, U1.4 (M2), U1.20 (VBG)
/INDUCTOR_IN_L1: C23.1, C24.2, L1.1, U1.27 (OUT_D_27), U1.28 (OUT_D_28), U1.35 (OUT_B)
/INDUCTOR_IN_L2: C11.2, C25.1, L2.1, U1.32 (OUT_C), U1.39 (OUT_A_39), U1.40 (OUT_A_40)
GND: C1.2, C2.2, C3.2, C4.2, C5.2, C8.2, C9.2, C10.2, C12.2, C13.1, C14.2, C15.1, C16.2, C17.2, C18.1, C19.1, C20.2, C26.2, C27.1, C28.2, C29.1, C30.2, C31.2, C32.2, C33.2, C34.2, C35.2, C36.2, C37.2, C38.2, C39.2, J1.1, J1.3, J2.1, J2.3, J3.1, J4.1, J5.2, R3.1, R4.1, R7.2, R8.1, U1.3 (M1), U1.12 (GND_12), U1.13 (GND_13), U1.16 (INPUT_C), U1.17 (INPUT_D), U1.25 (GND_25), U1.26 (GND_26), U1.33 (GND_33), U1.34 (GND_34), U1.41 (GND_41), U1.42 (GND_42), U2.2 (GND), U9.3 (GND), U10.3 (GND)
unnamed: C15.2, C18.2, C19.2, C21.2, L2.2, LS1.1
unnamed: C16.1, C17.1, C20.1, C22.1, L1.2, LS1.2
unnamed: C21.1, R7.1
unnamed: C22.2, R8.2
unnamed: C6.1, J6.1, U10.1 (IO1)
unnamed: C7.1, J6.2, U9.2 (IO2)
unnamed: TP1.1, U1.19 (~FAULT)
unnamed: TP2.1, U1.21 (~CLIP_OTW)
unnamed: C8.1, U1.14 (AVDD)
unnamed: C12.1, U1.15 (C_START)
unnamed: C9.1, U1.11 (DVDD)
unnamed: R4.2, U1.8 (FREQ_ADJ)
unnamed: C5.1, R1.2, U1.1 (GVDD_AB)
unnamed: C13.2, R5.1, U1.22 (GVDD_CD)
unnamed: R3.2, U1.7 (OC_ADJ)
unnamed: C32.1, R6.1, U1.18 (~RESET)

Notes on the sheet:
CONNECTOR DECOUPLING
24 -> 12V CONVERTOR
POWER INPUT AND OUTPUT
WAVE FORGE
SHOYU REV ONE
POWER AMP + AUDIO IN + SPEAKER
